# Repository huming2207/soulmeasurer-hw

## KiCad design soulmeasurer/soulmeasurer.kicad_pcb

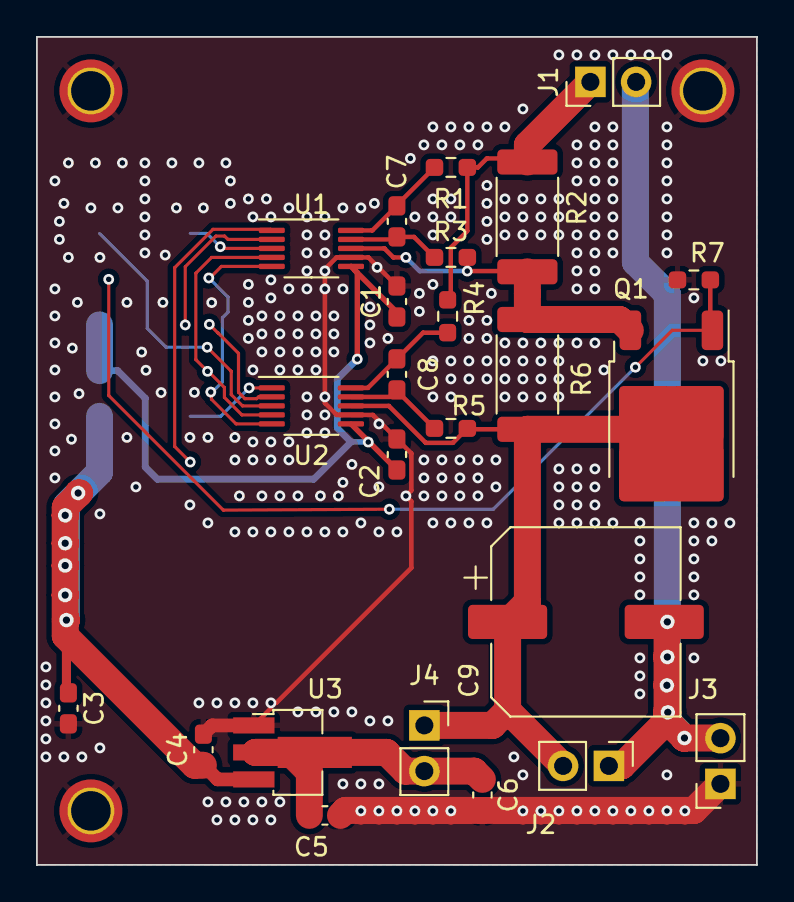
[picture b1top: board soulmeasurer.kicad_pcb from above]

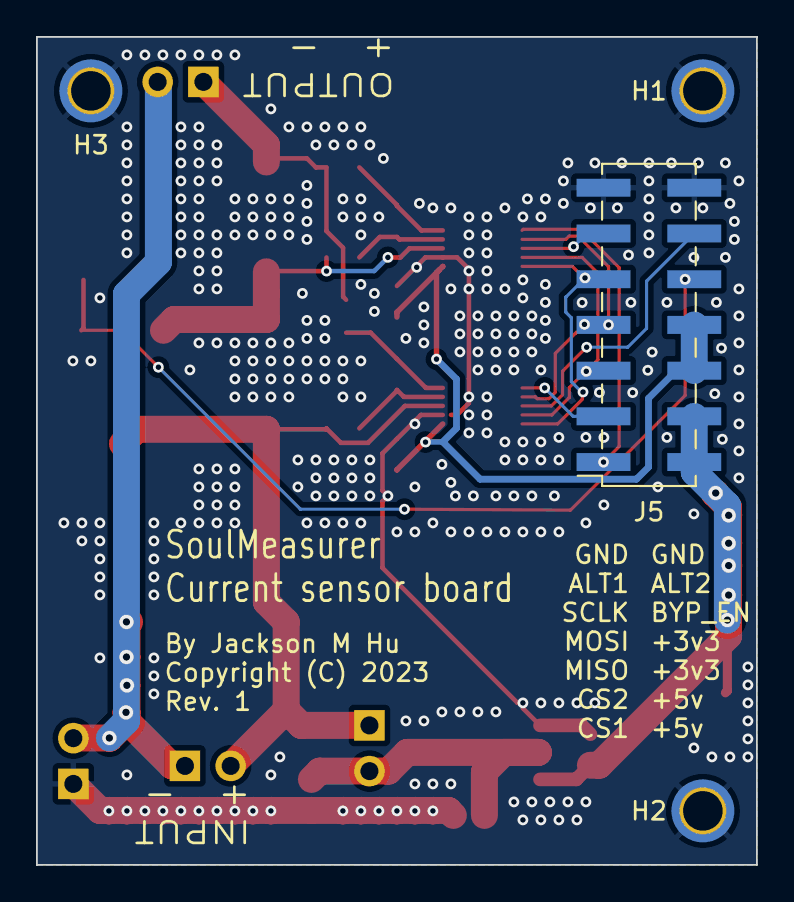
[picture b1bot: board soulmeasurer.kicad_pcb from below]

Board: 2 copper layers, 40.0 x 46.0 mm, 28 parts (4 on the bottom side), 20 nets.

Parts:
C1, C2, C4, C5, C7, C8: 0.1uF; C_0603_1608Metric_Pad1.08x0.95mm_HandSolder
C3, C6: 10uF; C_0603_1608Metric_Pad1.08x0.95mm_HandSolder
C9: 220uF; CP_Elec_10x12.6
H1, H2, H3: M3_Hole; MountingHole_2.2mm_M2_ISO7380_Pad_TopBottom
J1: OUTPUT; PinHeader_1x02_P2.54mm_Vertical
J2: INPUT; PinHeader_1x02_P2.54mm_Vertical
J3: LDO_GND; PinSocket_1x02_P2.54mm_Vertical
J4: LDO_VCC; PinSocket_1x02_P2.54mm_Vertical
J5: COMM; PinSocket_2x07_P2.54mm_Vertical_SMD
Q1: AP2055K; TO-252-2
R1, R3, R4, R5: 47R; R_0603_1608Metric_Pad0.98x0.95mm_HandSolder
R2: 0.05R; R_2512_6332Metric_Pad1.40x3.35mm_HandSolder
R6: 10R; R_2512_6332Metric_Pad1.40x3.35mm_HandSolder
R7: 10k; R_0603_1608Metric_Pad0.98x0.95mm_HandSolder
U1, U2: INA229-Q1; VSSOP-10_3x3mm_P0.5mm
U3: AMS1117/WL9005P3; SOT-89-3_Handsoldering

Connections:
+3.3VADC: C5.1, C6.1, J4.2, U3.2 (VO)
+3V3: C1.1, C2.1, J5.6, J5.8, U1.6 (VS), U2.6 (VS)
+5V: C3.1, C4.1, J5.2, J5.4, U3.3 (VI)
ALERT1: J5.11, U1.3 (ALERT)
ALERT2: J5.12, U2.3 (ALERT)
CS1: J5.1, U1.1 (CS)
CS2: J5.3, U2.1 (CS)
GND: C1.2, C2.2, C3.2, C4.2, C5.2, C6.2, H1.1, H2.1, H3.1, J3.1, J5.13, J5.14, R7.2, U1.7 (GND), U2.7 (GND), U3.1 (GND)
HI_CURR_BYPASS: J5.10, Q1.1 (G), R7.1
IN1+: C7.1, R1.1, U1.10 (IN_P)
IN1-: C7.2, R3.1, U1.9 (IN_N)
IN2+: C8.1, R4.1, U2.10 (IN_P)
IN2-: C8.2, R5.1, U2.9 (IN_N)
MISO: J5.5, U1.4 (MISO), U2.4 (MISO)
MOSI: J5.7, U1.2 (MOSI), U2.2 (MOSI)
unnamed: J1.1, R1.2, R2.2, R4.2
unnamed: C9.2, J1.2, J2.1, J3.2
SCLK: J5.9, U1.5 (SCLK), U2.5 (SCLK)
VBUS1: Q1.3 (S), R2.1, R3.2, R6.2, U1.8 (VBUS)
VBUS2: C9.1, J2.2, J4.1, Q1.2 (D), R5.2, R6.1, U2.8 (VBUS)

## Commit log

2023-04-21 Init
2023-05-05 Rev 1.0: fix schematic
2023-05-05 Finalise rev 1.0
2023-05-05 Add panel
2023-05-05 Rev 1: typo fixes
2023-05-05 Add gerber
2023-05-05 Rev 1: add BOM & PDF

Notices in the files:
soulmeasurer/soulmeasurer.kicad_pcb:
Copyright (C) 2023
